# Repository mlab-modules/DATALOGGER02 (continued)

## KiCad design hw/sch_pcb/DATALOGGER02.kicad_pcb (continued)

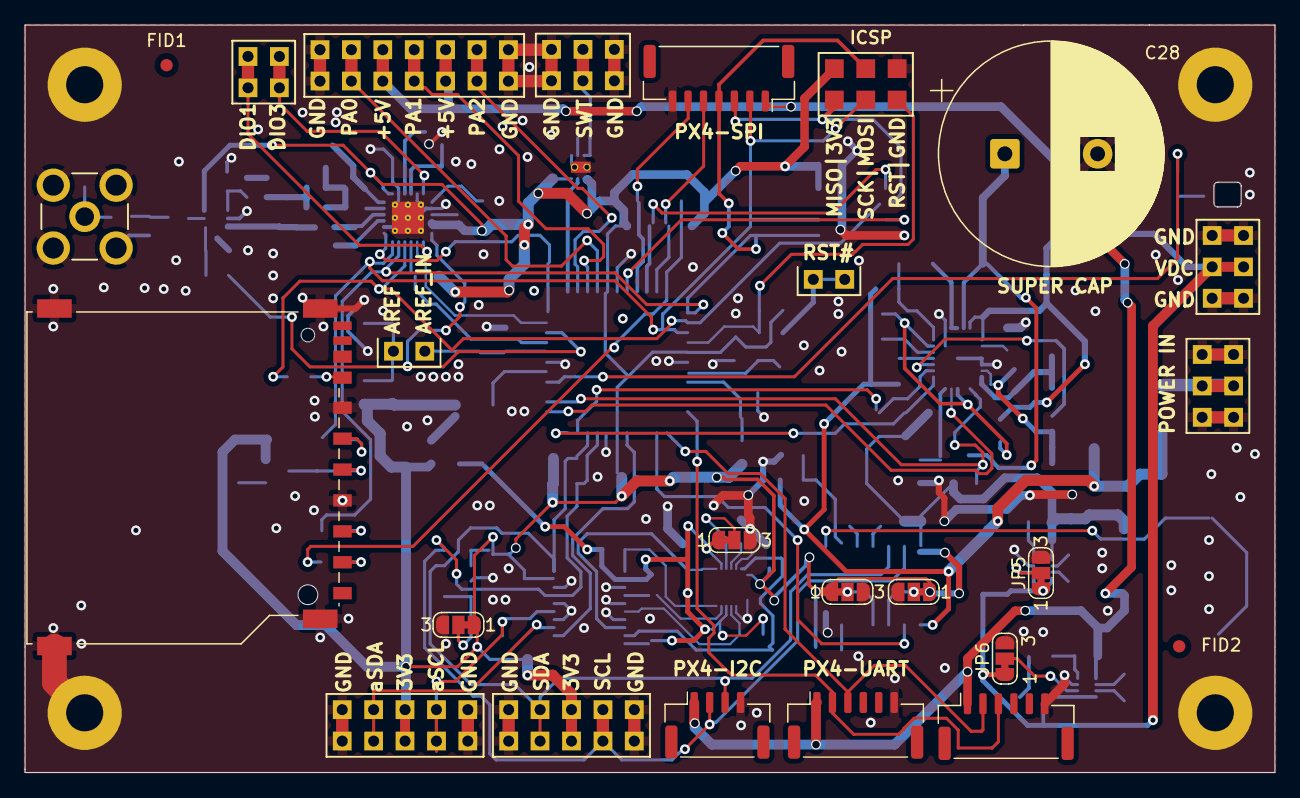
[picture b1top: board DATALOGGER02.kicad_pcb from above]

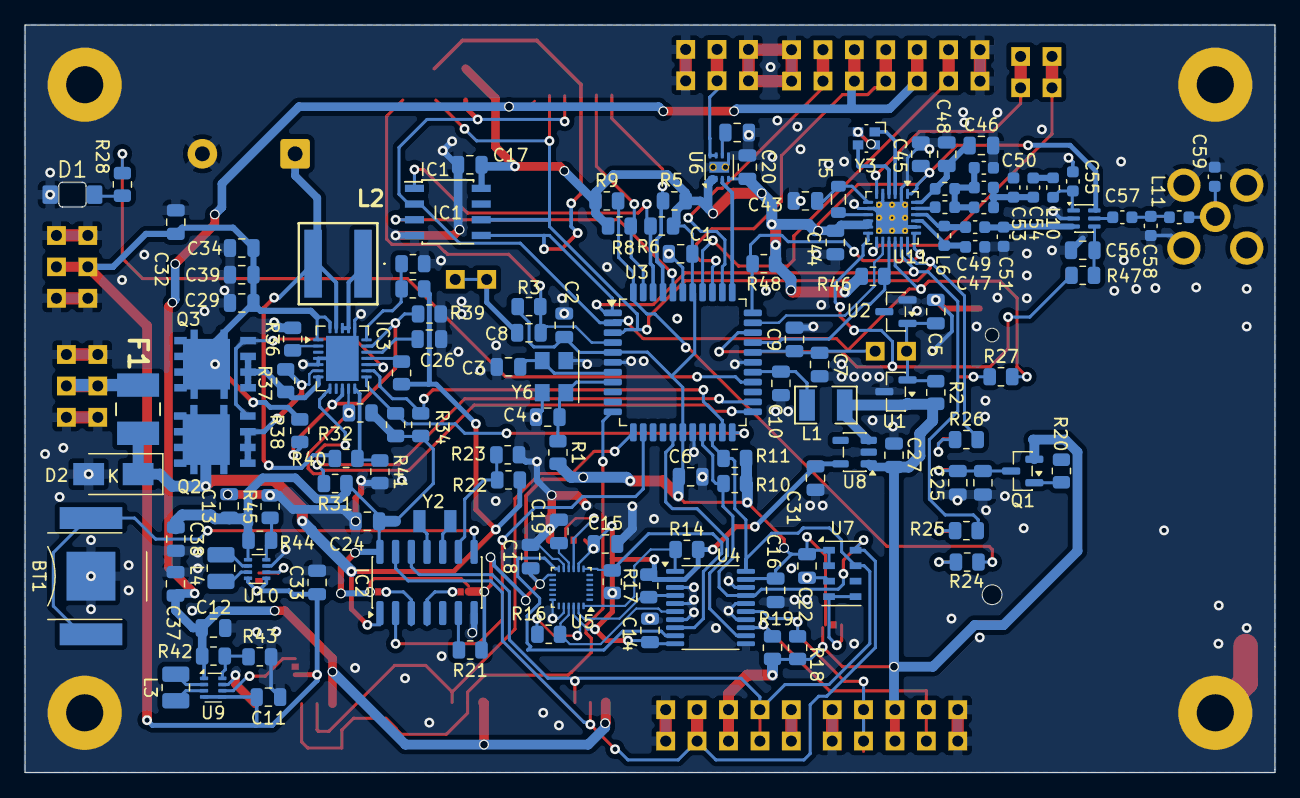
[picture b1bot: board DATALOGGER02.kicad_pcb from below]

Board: 2 copper layers, 101.1 x 60.5 mm, 161 parts (132 on the bottom side), 105 nets.

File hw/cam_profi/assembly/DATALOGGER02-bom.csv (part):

Component,Description,Part,References,Value,Footprint,Quantity Per PCB,Datasheet,ust_id,mfpn,height,mouser part number,mouser price/stock,manufacturer_name,manufacturer_part_number
1,,Battery_Cell-device,BT1,Battery_Cell-device 3V,BatteryHolder_Keystone_2998_1x6.8mm,1,,5c70984412875079b91f87ec,,,,,,
2,,C-Device-ISM02A-rescue,C47,1p8,C_0603_1608Metric,1,,5dad52a4128750448eca18e8,"C0G 0,1pF 50V",,,,,
3,,C-Device-ISM02A-rescue,C55,2p2,C_0603_1608Metric,1,,5c70984812875079b91f8bdd,"C0G 0,1pF 50V",,,,,
4,,C-Device-ISM02A-rescue,C49,2p4,C_0603_1608Metric,1,,5dad53d8128750448eca1906,"C0G 0,1pF 50V",,,,,
5,,C-Device-ISM02A-rescue,C52C58C59,3p3,C_0603_1608Metric,3,,5cd09016128750448e45434f,"C0G 0,1pF 50V",,,,,
6,,C-Device-ISM02A-rescue,C53,5p6,C_0603_1608Metric,1,,5dad5450128750448eca1919,"C0G 0,25pF 50V",,,,,
7,,C-device,C3C4,15pF,C_0805_2012Metric,2,,5c70984712875079b91f8b32,,,,,,
8,,C-Device-ISM02A-rescue,C54C57,39pF,C_0603_1608Metric,2,,5dad549f128750448eca1926,C0G 5% 50V,,,,,
9,,C-Device-ISM02A-rescue,C48,47pF,C_0805_2012Metric,1,,5dad5314128750448eca18f7,C0G 5% 50V,,,,,
10,,C-device,C21,1nF,C_0805_2012Metric,1,,5c70984712875079b91f8b45,,,,,,
11,Unpolarized capacitor,C,C26C56,1nF,C_0805_2012Metric,2,,5c70984812875079b91f8bec,,,,,,
12,,C-Device-ISM02A-rescue,C46,47nF,C_0805_2012Metric,1,,5dad51cf128750448eca18d8,X7R 1% 16V,,,,,
13,,C-device,C1C2C5C6C9C10C17C25C32C37C38,100nF,C_0805_2012Metric,11,,5c70984712875079b91f8b4c,,,,,,
14,Unpolarized capacitor,C,C14C15C16C18C19C22C24,100nF,C_0805_2012Metric,7,,5c70984712875079b91f8b4c,,,,,,
15,,C-Device-ISM02A-rescue,C45,100nF,C_0805_2012Metric,1,,5c70984812875079b91f8bf2,,,,,,
16,,C-Device-ISM02A-rescue,C43,470nF,C_0805_2012Metric,1,,5dad50c1128750448eca18c6,X5R 10% 10V,,,,,
17,,C-device,C20,1uF,C_0805_2012Metric,1,,5c70984712875079b91f8b50,,,,,,
18,Unpolarized capacitor,C,C27C31,1uF,C_0805_2012Metric,2,,5c70984712875079b91f8b50,,,,,,
19,,C-Device-ISM02A-rescue,C44,1uF,C_0805_2012Metric,1,,5c70984812875079b91f8bc2,,,,,,
20,,C-device,C8,4u7,C_0805_2012Metric,1,,5c70984712875079b91f8b52,,,,,,
21,,C-device,C7C23,10uF,C_0805_2012Metric,2,,5c70984812875079b91f8bbd,,,,,,
22,"Unpolarized capacitor, small symbol",C_Small,C11C33C39,22uF,C_0805_2012Metric,3,,650b58f1462c6d9e7205463b,,,,,,
23,"Unpolarized capacitor, small symbol",C_Small,C12C13C29C34,47uF,C_0805_2012Metric,4,,5c70984812875079b91f8bbf,,,,,,
24,,C-Device-ISM02A-rescue,C50C51,-,C_0603_1608Metric,2,,,,,,,,
25,Unpolarized capacitor,C,C28,50F,CP_Radial_D18.0mm_P7.50mm,1,,,,,,,,
26,,LED-device,D1,HLMP-K150+FIX-LED-313,LED_1206_mill,1,,5c70984712875079b91f8b67,,,,,,
27,,D-device,D2,M4,Diode-SMA_Standard,1,,5c70984512875079b91f88ac,,,,,,
28,,Polyfuse-device,F1,1.2A,1812,1,,5c70984512875079b91f88d2,,,,,,
29,F-RAM Excelon LP 40 MHz 8-EIAJ,CY15B108QN-40SXI,IC1,CY15B108QN-40SXI,SOIC-8_3.9x4.9mm_Pitch1.27mm,1,https://www.mouser.in/datasheet/2/196/CYPR_S_A0011123055_1-3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,,,2.03,727-CY15B108QN-40SXI,https://www.mouser.co.uk/ProductDetail/Infineon-Cypress/CY15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,Infineon / Cypress,CY15B108QN-40SXI
30,-40C to +85C Integrated Processor Companion with Memory 14-pin SOIC Package,FM3164-S,IC2,FM3164-G,SOIC-14_3.9x8.7mm_P1.27mm,1,https://www.tme.eu/Document/fd7387082c26a47b1cfc6f4ba6bd97fb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,,,1.75,,,RAMTRON,FM3164-S
31,Power Management Specialized - PMIC 2.5A Supercapacitor Backup Power Manager,LTC4041EUFD#PBF,IC3,LTC4041EUFD#PBF,QFN-24-1EP_4x5mm_P0.5mm_EP2.65x3.65mm,1,https://www.analog.com/media/en/technical-documentation/data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,,,0.8,584-4041EUFDPB,https://www.mouser.co.uk/ProductDetail/Analog-Devices/LTC404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,Analog Devices,LTC4041EUFD#PBF
32,"Generic connector, single row, 01x04, script generated (kicad-library-utils/schlib/autogen/connector/)",Conn_01x04_Female,J9,Conn_01x04_Female,JST_GH_SM04B-GHS-TB_1x04-1MP_P1.25mm_Horizontal,1,,,,,,,,
33,"Generic connector, single row, 01x06, script generated (kicad-library-utils/schlib/autogen/connector/)",Conn_01x06_Female,J7J14,Conn_01x06_Female,JST_GH_SM06B-GHS-TB_1x06-1MP_P1.25mm_Horizontal,2,,,,,,,,
34,"Generic connector, single row, 01x07, script generated (kicad-library-utils/schlib/autogen/connector/)",Conn_01x07_Female,J8,Conn_01x07_Female,JST_GH_SM07B-GHS-TB_1x07-1MP_P1.25mm_Horizontal,1,,,,,,,,
35,,HEADER_2x01-MLAB_HEADER,J2,HEADER_2x01,Straight_2x01,1,,,,,,,,
36,,HEADER_2x01_PARALLEL-MLAB_HEADER,J1,HEADER_2x01_PARALLEL,Straight_2x01,1,,,,,,,,
37,"2x02 2.54 mm pitch header, 2 pins next to each other are connected",HEADER_2x02_PARALLEL,J13,HEADER_2x02_PARALLEL,Straight_2x02,1,,,,,,,,
38,,HEADER_2x03-MLAB_HEADER,J3,HEADER_2x03,SMD_2x03_WO_paste,1,,,,,,,,
39,"2x03 2.54 mm pitch header, 2 pins next to each other are connected",HEADER_2x03_PARALLEL,J5J24,HEADER_2x03_PARALLEL,Straight_2x03,2,,,,,,,,
40,,HEADER_2x03_PARALLEL-MLAB_HEADER,J4,HEADER_2x03_PARALLEL,Straight_2x03,1,,,,,,,,
41,"2x05 2.54 mm pitch header, 2 pins next to each other are connected",HEADER_2x05_PARALLEL,J10J12,HEADER_2x05_PARALLEL,Straight_2x05,2,,,,,,,,
42,"2x07 2.54 mm pitch header, 2 pins next to each other are connected",HEADER_2x07_PARALLEL,J11,HEADER_2x07_PARALLEL,Straight_2x07,1,,,,,,,,
43,,SD_Card-Connector,J6,MCC-SD (kouka z modulu),MCC-SD,1,http://portal.fciconnect.com/Comergent//fci/drawing/10067847.pdf,,,,,,,
44,,SMA-MLAB_CONNECTORS,J23,MCX,MCX,1,,,,,,,,
45,,L-Device-ISM02A-rescue,L7,0R,L_0603_1608Metric,1,,5c70984512875079b91f8949,,,,,,
46,,L-Device-ISM02A-rescue,L9,2n4,L_0603_1608Metric,1,,5dad56ff128750448eca1975,LQW15AN2N5C00D,,,,,
47,,L-Device-ISM02A-rescue,L10,4n7,L_0603_1608Metric,1,,671226edd509c19f2ce8ed2d,LQW15AN4N7C00D,,,,,
48,,L-Device-ISM02A-rescue,L11,9n1,L_0603_1608Metric,1,,5dad5789128750448eca1995,LQW15AN9N1H00D,,,,,
49,,L-Device-ISM02A-rescue,L6,15nH,L_0603_1608Metric,1,,5dad566c128750448eca1959,LQW15AN15NH00D,,,,,
50,,L-Device-ISM02A-rescue,L8,47nH,L_0603_1608Metric,1,,5dad56ba128750448eca1968,LQW15AN47NJ00D,,,,,
51,,L_Small-Device-ISM02A-rescue,L5,15uH,L_0805_2012Metric,1,,5dad55e8128750448eca1941,MLZ2012M150W 0805,,,,,
52,,L-device,L1,10uH - LQH32CN100K23L,SMD-1210,1,,5c70984412875079b91f87ff,,,,,,
53,Inductor,L,L3L4,1uH - DFE252012P-1R0M=P2,L_1008_2520Metric,2,,,,,,,,
54,Inductor,L,L2,XAL-6030-182 1.8 uH,XAL6030181MEC,1,,,,,,,,
55,"-4.3A Id, -12V Vds, 50mOhm Rds, P-Channel HEXFET Power MOSFET, SOT-23",IRLML6401,Q1,DMP2045UQ-7,SOT-23,1,https://www.infineon.com/dgdl/irlml6401pbf.pdf?fileId=5546d4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,,,,,,,
56,"N-MOSFET transistor, source/gate/drain",Q_NMOS_SGD,Q2Q3,DMTH3002LPS,D_POWERDI5060-8_6.0x5.1mm_P1.27mm,2,https://eu.mouser.com/datasheet/2/115/DIOD_S_A0003132884_1-2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,669990696fdfe6f54e2eb28a,,,,,,DMT31M7LPS-13
57,Resistor,R,R37,25mR,R_0805_2012Metric,1,,,,,,,,
58,,R-device,R24R25R26R27,100,R_0805_2012Metric,4,,5c70984512875079b91f8977,,,,,,
59,Resistor,R,R47,100R,R_0805_2012Metric,1,,5c70984512875079b91f8956,,,,,,
60,Resistor,R,R20,470R,R_0805_2012Metric,1,,,,,,,,
61,Resistor,R,R36,2k,R_0805_2012Metric,1,,,,,,,,
62,,R-device,R28,2k2,R_0805_2012Metric,1,,5c70984612875079b91f8990,,,,,,
63,,R-device,R2,4k7,R_0805_2012Metric,1,,5c70984612875079b91f8995,,,,,,
64,Resistor,R,R5R6R8R9R10R11R14R15R16R17R18R19R21R48,10k,R_0805_2012Metric,14,,5c70984612875079b91f899f,,,,,,
65,,R-device,R3,10k,R_0805_2012Metric,1,,5c70984612875079b91f899f,,,,,,
66,,R-Device-ISM02A-rescue,R46,10k,R_0805_2012Metric,1,,5c70984512875079b91f8962,,,,,,
67,Resistor,R,R23R30,56k,R_0805_2012Metric,2,,,,,,,,
68,Resistor,R,R43R45,91k,R_0805_2012Metric,2,,,,,,,,
69,Resistor,R,R32R33R34R39R41,100k,R_0805_2012Metric,5,,,,,,,,
70,Resistor,R,R22R29,150k,R_0805_2012Metric,2,,,,,,,,
71,Resistor,R,R40,220k,R_0805_2012Metric,1,,,,,,,,
72,Resistor,R,R44,511k,R_0805_2012Metric,1,,,,,,,,
73,Resistor,R,R42,806k,R_0805_2012Metric,1,,,,,,,,
74,Resistor,R,R31,1M,R_0805_2012Metric,1,,,,,,,,
75,,R-device,R1,-,R_0805_2012Metric,1,,,,,,,,
76,Resistor,R,R38,523k (E96),R_0805_2012Metric,1,,,,,,,,
77,Resistor,R,R35,6.2k 1/8W,R_0805_2012Metric,1,,,,,,,,
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
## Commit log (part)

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2025-09-06 Update project to KiCADv9.
2025-09-06 Update metadata files
2025-09-06 Update actions products
2026-01-18 Desing improvements WIP.

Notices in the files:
hw/sch_pcb/DATALOGGER02.kicad_pcb:
GPL 3.0
